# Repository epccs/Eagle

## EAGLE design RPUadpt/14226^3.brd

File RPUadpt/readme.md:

[RPUadpt]

Shield to interface microcontrollers to a managed multidrop serial.

[RPUadpt]: https://github.com/epccs/RPUadpt/

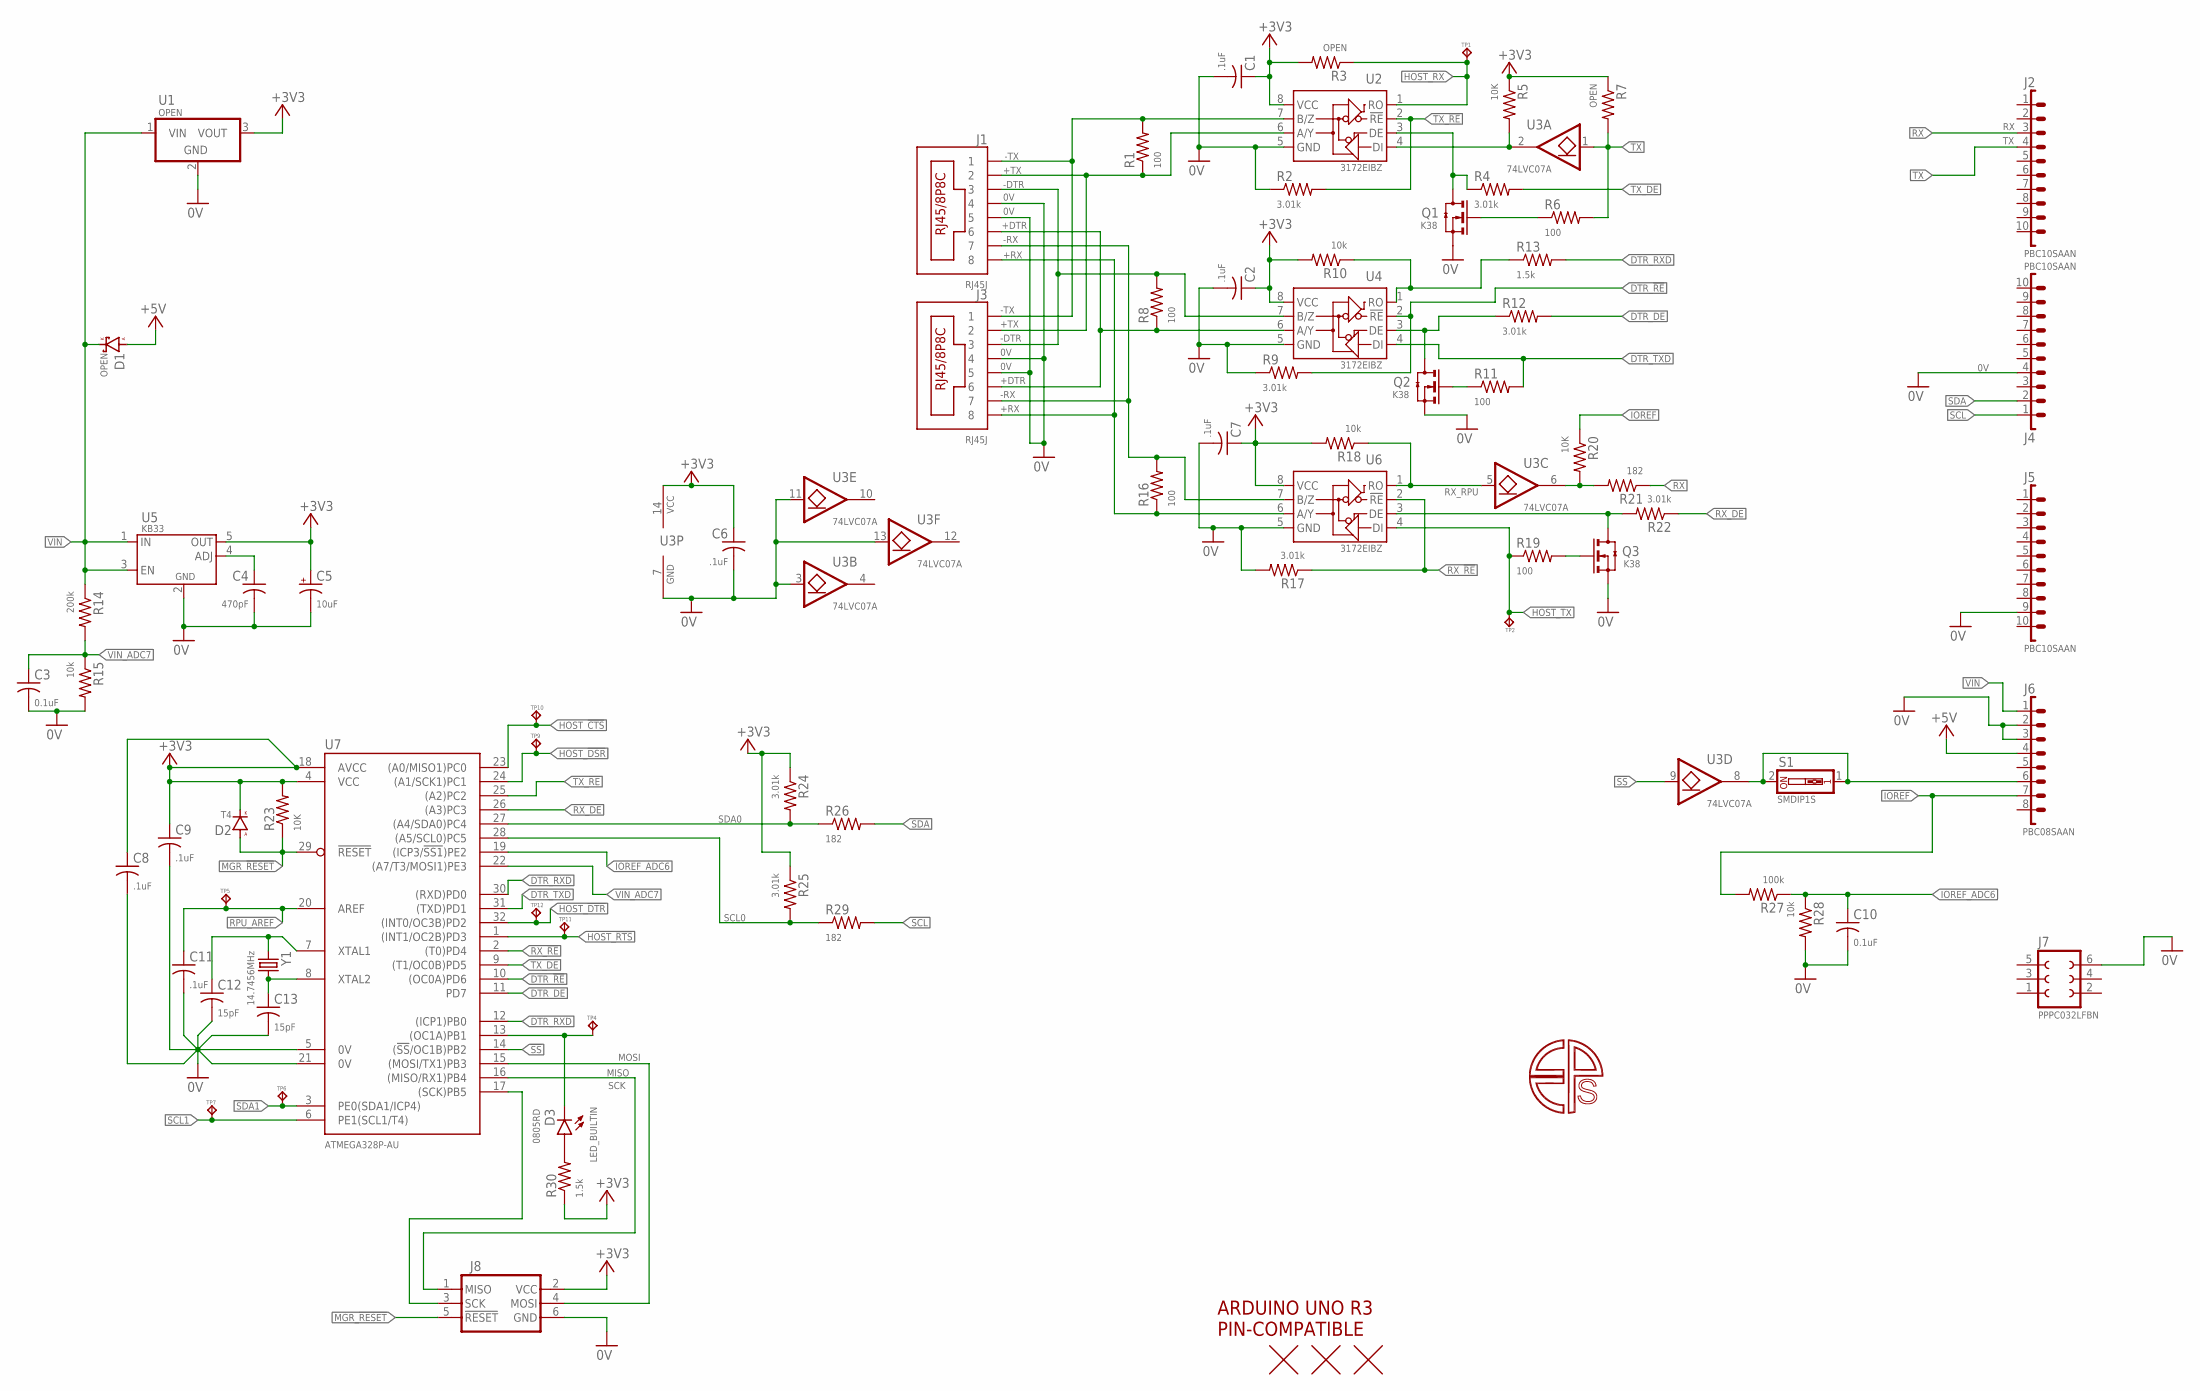
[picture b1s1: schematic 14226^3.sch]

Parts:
C1, C2, C6, C7, C8, C9, C11: .1uF; C0603(1608)
C3, C10: 0.1uF; C0603(1608)
C4: 470pF; C0603(1608)
C5: 10uF; 3216
C12, C13: 15pF; C0603(1608)
D1: OPEN; SMA
D2: T4; SOD123
D3: 0805RD; C0805(2012)
J1, J3: RJ45J; RJ45-8HZT
J2, J4, J5: PBC10SAAN; 1X10
J6: PBC08SAAN; 1X8
J7: PPPC032LFBN; F2X3
J8: ISP-SPIPTH; ISP
Q1, Q2, Q3: K38; SOT23
R1, R6, R8, R11, R16, R19: 100; C0805(2012)
R2, R4, R9, R12, R17, R22, R24, R25: 3.01k; C0805(2012)
R3, R7: OPEN; C0805(2012)
R5, R20, R23: 10K; C0805(2012)
R10, R15, R18, R28: 10k; C0805(2012)
R13, R30: 1.5k; C0805(2012)
R14: 200k; C0805(2012)
R21, R26, R29: 182; C0805(2012)
R27: 100k; C0805(2012)
S1: SMDIP1S; SMD-DIPSWITCH-1
TP1, TP2, TP4, TP5, TP6, TP7, TP9, TP10, TP11, TP12: TPPAD1-08; P1-08
U1: OPEN; OKI-78SR-H
U2, U4, U6: 3172EIBZ; SOIC8
U3: 74LVC07A; 14SOIC
U5: KB33; SOT23-5,SOT25
U7: ATMEGA328P-AU; TQFP32-08
U$1: ARDUINO-UNO; ARDUINO_UNO
U$2, U$3, U$4: FIDUCIAL1.27; FIDUCIAL-1.27
Y1: 14.7456MHz; CSM-3X

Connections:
0V: C1.2, C2.2, C3.2, C4.2, C5.-, C6.2, C7.2, C8.2, C9.2, C10.2, C11.2, C12.2, C13.2, J1.4, J1.5, J3.4, J3.5, J4.4, J5.9, J6.2, J6.3, J7.6, J8.6 (GND), Q1.2(S) (S), Q2.2(S) (S), Q3.2(S) (S), R2.1, R9.1, R15.2, R17.2, R28.2, U1.2 (GND), U2.5 (GND), U3.3 (I), U3.7 (GND), U3.11 (I), U3.13 (I), U4.5 (GND), U5.2 (GND), U6.5 (GND), U7.5 (0V), U7.21 (0V)
!SS!: U3.9 (I), U7.14 ((!SS!/OC1B)PB2)
+3V3: C1.1, C2.1, C5.+, C6.1, C7.1, C8.1, C9.1, D2.C (K), J8.2 (VCC), R3.2, R5.1, R7.1, R10.2, R18.2, R23.2, R24.1, R25.1, R30.1, U1.3 (VOUT), U2.8 (VCC), U3.14 (VCC), U4.8 (VCC), U5.5 (OUT), U6.8 (VCC), U7.4 (VCC), U7.18 (AVCC)
+5V: D1.A, J6.4
+DTR: J1.6, J3.6, R8.1, U4.6 (A/Y)
+RX: J1.8, J3.8, R16.1, U6.6 (A/Y)
+TX: J1.2, J3.2, R1.1, U2.6 (A/Y)
-DTR: J1.3, J3.3, R8.2, U4.7 (B/Z)
-RX: J1.7, J3.7, R16.2, U6.7 (B/Z)
-TX: J1.1, J3.1, R1.2, U2.7 (B/Z)
DTR_!RE: R9.2, U4.2 (!RE), U7.10 ((OC0A)PD6)
DTR_DE: R12.2, U7.11 (PD7)
DTR_RXD: R13.2, U7.12 ((ICP1)PB0), U7.30 ((RXD)PD0)
DTR_TXD: R11.2, U4.4 (DI), U7.31 ((TXD)PD1)
HOST_!CTS: TP10.TP, U7.23 ((A0/MISO1)PC0)
HOST_!DSR: TP9.TP, U7.24 ((A1/SCK1)PC1)
HOST_!DTR: TP12.TP, U7.32 ((INT0/OC3B)PD2)
HOST_!RTS: TP11.TP, U7.1 ((INT1/OC2B)PD3)
HOST_RX: R3.1, TP1.TP, U2.1 (RO)
HOST_TX: R19.1, TP2.TP, U6.4 (DI)
IOREF: J6.7, R20.1, R27.2
IOREF_ADC6: C10.1, R27.1, R28.1, U7.19 ((ICP3/!SS1!)PE2)
LED_BUILTIN: D3.K, TP4.TP, U7.13 ((OC1A)PB1)
MGR_!RESET: D2.A, J8.5 (!RESET), R23.1, U7.29 (!RESET)
MISO: J8.1 (MISO), U7.16 ((MISO/RX1)PB4)
MOSI: J8.4 (MOSI), U7.15 ((MOSI/TX1)PB3)
unnamed: J6.6, S1.1, S1.2, U3.8 (O)
unnamed: R20.2, R21.2, U3.6 (O)
unnamed: Q3.3(D) (D), R22.2, U6.3 (DE)
unnamed: Q1.1(G) (G), R6.1
unnamed: Q1.3(D) (D), R4.1, U2.3 (DE)
unnamed: R10.1, R13.1, U4.1 (RO)
unnamed: Q2.3(D) (D), R12.1, U4.3 (DE)
unnamed: Q2.1(G) (G), R11.1
unnamed: C4.1, U5.4 (ADJ)
unnamed: Q3.1(G) (G), R19.2
unnamed: D3.A, R30.2
RPU_AREF: C11.1, TP5.TP, U7.20 (AREF)
RX: J2.3, R21.1
RX_!RE: R17.1, U6.2 (!RE), U7.2 ((T0)PD4)
RX_DE: R22.1, U7.26 ((A3)PC3)
RX_RPU: R18.1, U3.5 (I), U6.1 (RO)
SCK: J8.3 (SCK), U7.17 ((SCK)PB5)
SCL: J4.1, R29.2
SCL0: R25.2, R29.1, U7.28 ((A5/SCL0)PC5)
SCL1: TP7.TP, U7.6 (PE1(SCL1/T4))
SDA: J4.2, R26.2
SDA0: R24.2, R26.1, U7.27 ((A4/SDA0)PC4)
SDA1: TP6.TP, U7.3 (PE0(SDA1/ICP4))
TX: J2.4, R6.2, R7.2, U3.1 (I)
TX_!RE: R2.2, U2.2 (!RE), U7.25 ((A2)PC2)
TX_DE: R4.2, U7.9 ((T1/OC0B)PD5)
TX_RPU: R5.2, U2.4 (DI), U3.2 (O)
VIN: D1.K, J6.1, R14.1, U1.1 (VIN), U5.1 (IN), U5.3 (EN)
VIN_ADC7: C3.1, R14.2, R15.1, U7.22 ((A7/T3/MOSI1)PE3)
XTAL1: C12.1, U7.7 (XTAL1), Y1.1
XTAL2: C13.1, U7.8 (XTAL2), Y1.2

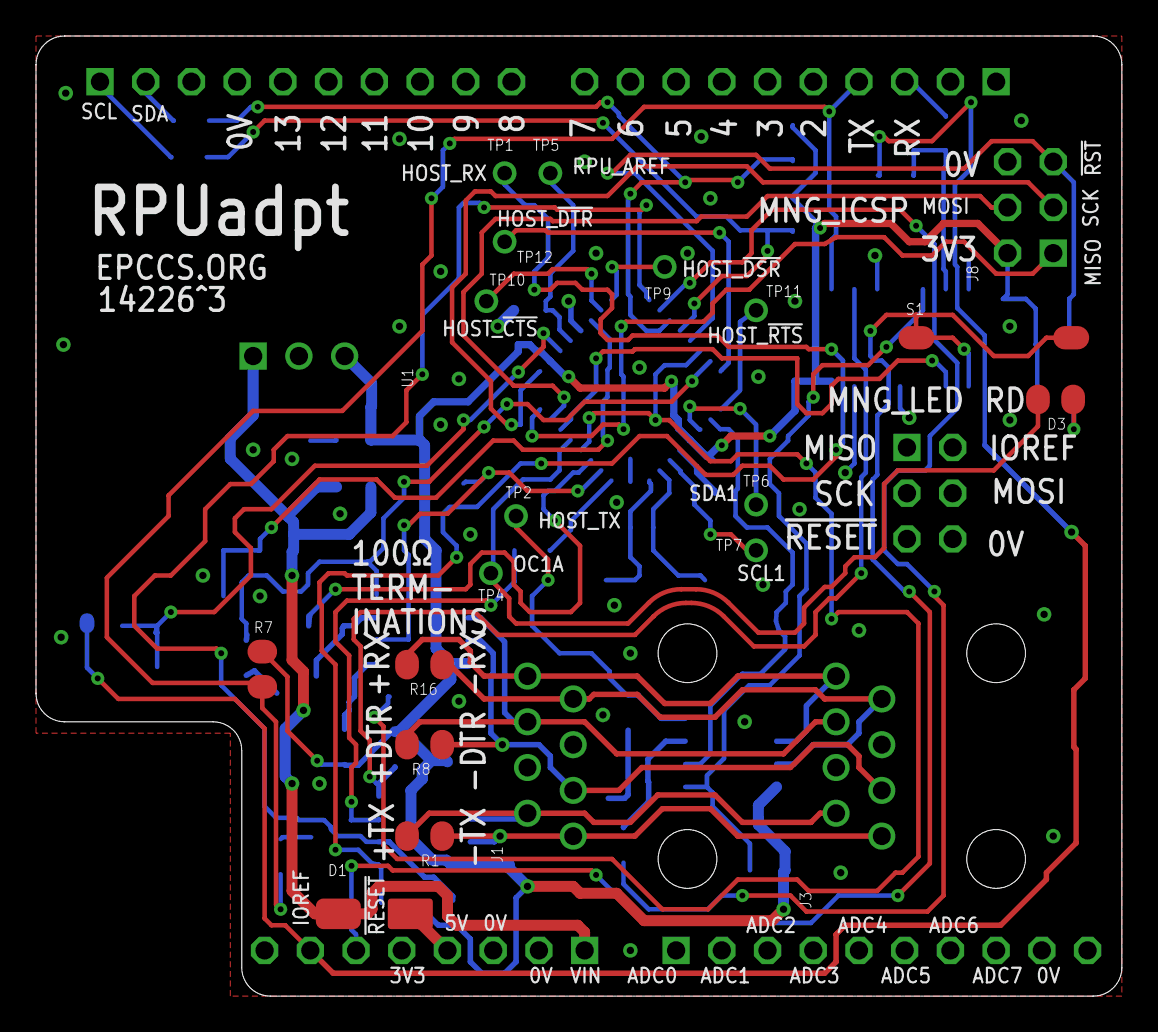
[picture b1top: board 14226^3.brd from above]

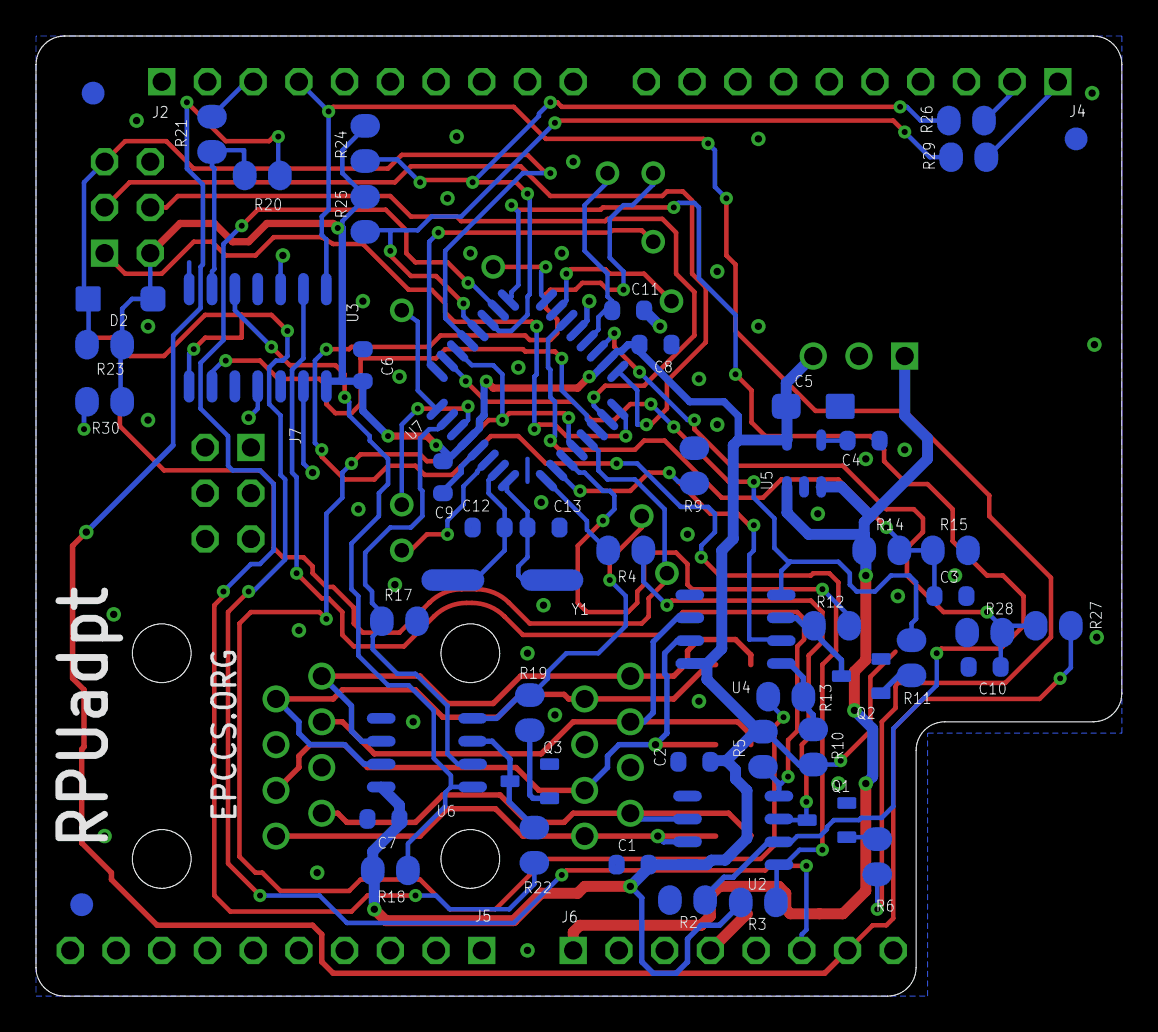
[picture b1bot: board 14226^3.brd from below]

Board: 2 copper layers, 60.3 x 53.3 mm, 80 parts (58 on the bottom side), 57 nets.

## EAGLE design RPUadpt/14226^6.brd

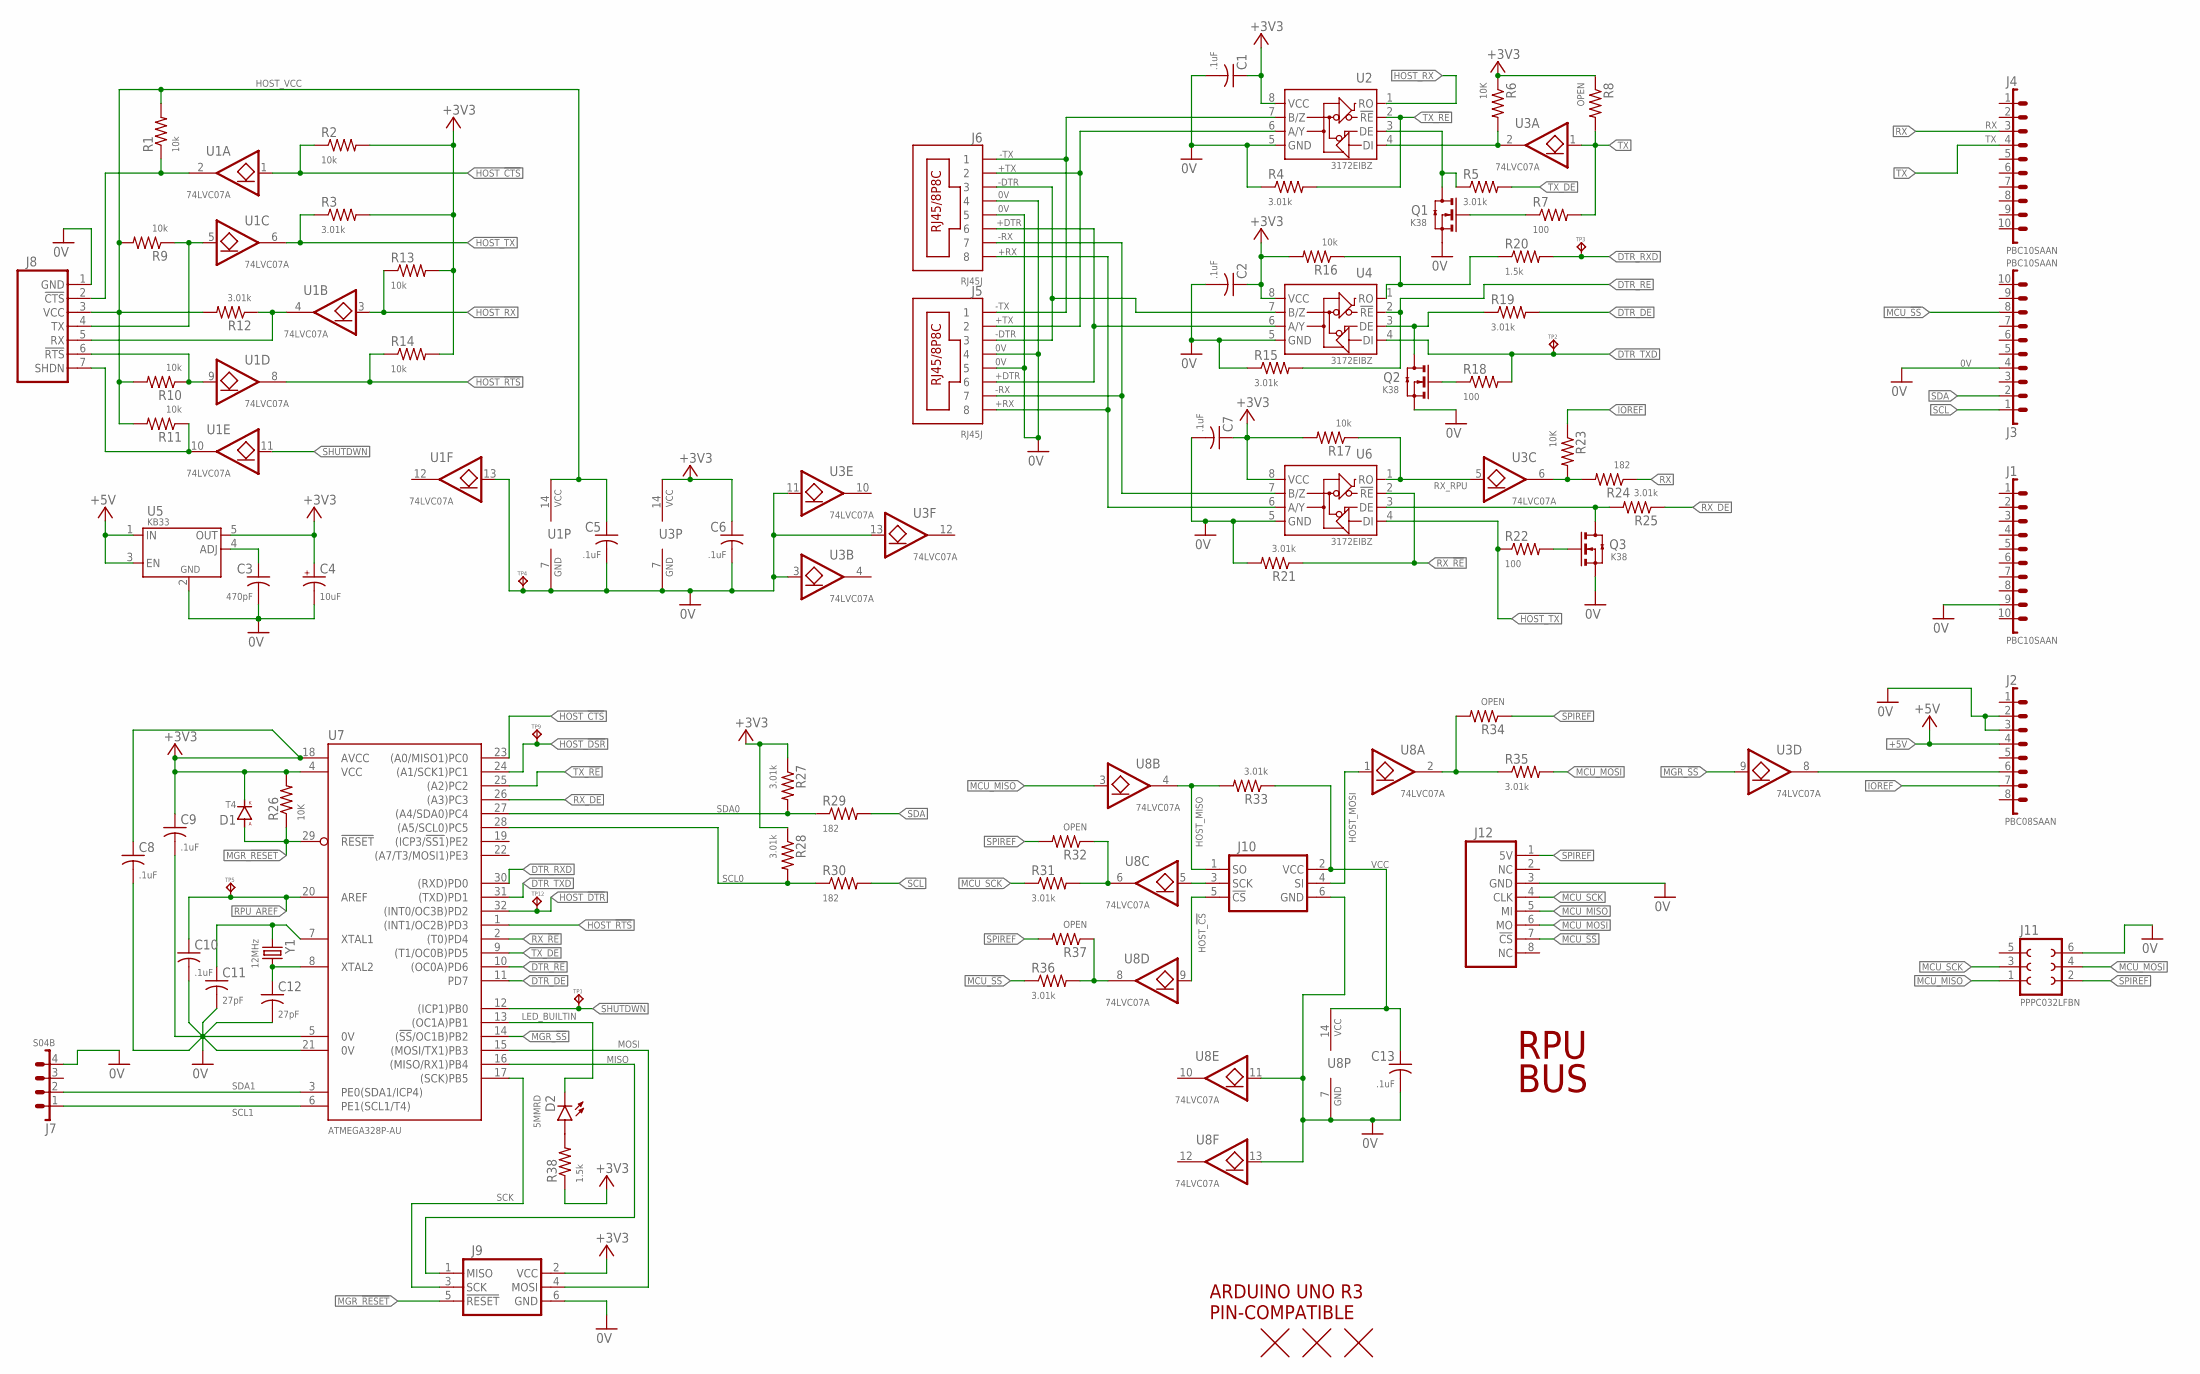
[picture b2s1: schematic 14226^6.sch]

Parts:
C1, C2, C5, C6, C7, C8, C9, C10, C13: .1uF; C0603(1608)
C3: 470pF; C0603(1608)
C4: 10uF; 3216
C11, C12: 27pF; C0603(1608)
D1: T4; SOD123
D2: 5MMRD; LED5MM
J1, J3, J4: PBC10SAAN; 1X10
J2: PBC08SAAN; 1X8
J5, J6: RJ45J; RJ45-8HZT
J7: S04B; B04B
J8: FTDI-FRIEND
J9: ISP-SPIPTH; ISP
J10: SPI; ISP
J11: PPPC032LFBN; F2X3
J12: MICRO-SD
Q1, Q2, Q3: K38; SOT23
R1, R2, R9, R10, R11, R13, R14, R16, R17: 10k; C0805(2012)
R3, R4, R5, R12, R15, R19, R21, R25, R27, R28, R31, R33, R35, R36: 3.01k; C0805(2012)
R6, R23, R26: 10K; C0805(2012)
R7, R18, R22: 100; C0805(2012)
R8, R32, R34, R37: OPEN; C0805(2012)
R20, R38: 1.5k; C0805(2012)
R24, R29, R30: 182; C0805(2012)
TP1, TP2, TP3, TP4, TP5, TP9, TP12: TPPAD1-08; P1-08
U1, U3, U8: 74LVC07A; 14SOIC
U2, U4, U6: 3172EIBZ; SOIC8
U5: KB33; SOT23-5,SOT25
U7: ATMEGA328P-AU; TQFP32-08
U$1: ARDUINO-UNO; ARDUINO_UNO
U$2, U$3, U$4: FIDUCIAL1.27; FIDUCIAL-1.27
Y1: 12MHz; CSM-3X

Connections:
0V: C1.2, C2.2, C3.2, C4.-, C5.2, C6.2, C7.2, C8.2, C9.2, C10.2, C11.2, C12.2, C13.2, J1.9, J2.2, J2.3, J3.4, J5.4, J5.5, J6.4, J6.5, J7.4, J8.1 (GND), J9.6 (GND), J10.6 (GND), J11.6, J12.3 (GND), Q1.2(S) (S), Q2.2(S) (S), Q3.2(S) (S), R4.1, R15.1, R21.2, TP4.TP, U1.7 (GND), U1.13 (I), U2.5 (GND), U3.3 (I), U3.7 (GND), U3.11 (I), U3.13 (I), U4.5 (GND), U5.2 (GND), U6.5 (GND), U7.5 (0V), U7.21 (0V), U8.7 (GND), U8.11 (I), U8.13 (I)
+3V3: C1.1, C2.1, C4.+, C6.1, C7.1, C8.1, C9.1, D1.C (K), J9.2 (VCC), R2.2, R3.2, R6.1, R8.1, R13.2, R14.2, R16.2, R17.2, R26.2, R27.1, R28.1, R38.1, U2.8 (VCC), U3.14 (VCC), U4.8 (VCC), U5.5 (OUT), U6.8 (VCC), U7.4 (VCC), U7.18 (AVCC)
+5V: J2.4, U5.1 (IN), U5.3 (EN)
+DTR: J5.6, J6.6, U4.6 (A/Y)
+RX: J5.8, J6.8, U6.6 (A/Y)
+TX: J5.2, J6.2, U2.6 (A/Y)
-DTR: J5.3, J6.3, U4.7 (B/Z)
-RX: J5.7, J6.7, U6.7 (B/Z)
-TX: J5.1, J6.1, U2.7 (B/Z)
DTR_!RE: R15.2, U4.2 (!RE), U7.10 ((OC0A)PD6)
DTR_DE: R19.2, U7.11 (PD7)
DTR_RXD: R20.2, TP3.TP, U7.30 ((RXD)PD0)
DTR_TXD: R18.2, TP2.TP, U4.4 (DI), U7.31 ((TXD)PD1)
HOST_!CS: J10.5 (!CS), U8.9 (I)
HOST_!CTS: R2.1, U1.1 (I), U7.23 ((A0/MISO1)PC0)
HOST_!DSR: TP9.TP, U7.24 ((A1/SCK1)PC1)
HOST_!DTR: TP12.TP, U7.32 ((INT0/OC3B)PD2)
HOST_!RTS: R14.1, U1.8 (O), U7.1 ((INT1/OC2B)PD3)
HOST_MISO: J10.1 (SO), R33.2, U8.4 (O)
HOST_MOSI: J10.4 (SI), U8.1 (I)
HOST_RX: R13.1, U1.3 (I), U2.1 (RO)
HOST_SCK: J10.3 (SCK), U8.5 (I)
HOST_TX: R3.1, R22.1, U1.6 (O), U6.4 (DI)
HOST_VCC: C5.1, J8.3 (VCC), R1.2, R9.2, R10.2, R11.2, R12.2, U1.14 (VCC)
IOREF: J2.7, R23.1
LED_BUILTIN: D2.K, U7.13 ((OC1A)PB1)
MCU_!SS!: J3.8, J12.7 (!CS), R36.1
MCU_MISO: J11.1, J12.5 (MI), U8.3 (I)
MCU_MOSI: J11.4, J12.6 (MO), R35.2
MCU_SCK: J11.3, J12.4 (CLK), R31.1
MGR_!RESET: D1.A, J9.5 (!RESET), R26.1, U7.29 (!RESET)
MGR_!SS!: U3.9 (I), U7.14 ((!SS!/OC1B)PB2)
MISO: J9.1 (MISO), U7.16 ((MISO/RX1)PB4)
MOSI: J9.4 (MOSI), U7.15 ((MOSI/TX1)PB3)
unnamed: J2.6, U3.8 (O)
unnamed: R34.2, R35.1, U8.2 (O)
unnamed: D2.A, R38.2
unnamed: R31.2, R32.1, U8.6 (O)
unnamed: R23.2, R24.2, U3.6 (O)
unnamed: Q3.3(D) (D), R25.2, U6.3 (DE)
unnamed: R36.2, R37.1, U8.8 (O)
unnamed: Q1.1(G) (G), R7.1
unnamed: Q1.3(D) (D), R5.1, U2.3 (DE)
unnamed: R16.1, R20.1, U4.1 (RO)
unnamed: Q2.3(D) (D), R19.1, U4.3 (DE)
unnamed: Q2.1(G) (G), R18.1
unnamed: C3.1, U5.4 (ADJ)
unnamed: Q3.1(G) (G), R22.2
RPU_AREF: C10.1, TP5.TP, U7.20 (AREF)
RX: J4.3, R24.1
RX_!RE: R21.1, U6.2 (!RE), U7.2 ((T0)PD4)
RX_DE: R25.1, U7.26 ((A3)PC3)
RX_RPU: R17.1, U3.5 (I), U6.1 (RO)
SCK: J9.3 (SCK), U7.17 ((SCK)PB5)
SCL: J3.1, R30.2
SCL0: R28.2, R30.1, U7.28 ((A5/SCL0)PC5)
SCL1: J7.1, U7.6 (PE1(SCL1/T4))
SDA: J3.2, R29.2
SDA0: R27.2, R29.1, U7.27 ((A4/SDA0)PC4)
SDA1: J7.2, U7.3 (PE0(SDA1/ICP4))
SHUTDWN: TP1.TP, U1.11 (I), U7.12 ((ICP1)PB0)
SPIREF: J11.2, J12.1 (5V), R32.2, R34.1, R37.2
TX: J4.4, R7.2, R8.2, U3.1 (I)
TX_!RE: R4.2, U2.2 (!RE), U7.25 ((A2)PC2)
TX_DE: R5.2, U7.9 ((T1/OC0B)PD5)
TX_RPU: R6.2, U2.4 (DI), U3.2 (O)
VCC: C13.1, J10.2 (VCC), R33.1, U8.14 (VCC)
XTAL1: C11.1, U7.7 (XTAL1), Y1.1
XTAL2: C12.1, U7.8 (XTAL2), Y1.2
_HOST_!CTS: J8.2 (!CTS), R1.1, U1.2 (O)
_HOST_!RTS: J8.6 (!RTS), R10.1, U1.9 (I)
_HOST_RX: J8.5 (RX), R12.1, U1.4 (O)
_HOST_SHDN: J8.7 (SHDN), R11.1, U1.10 (O)
_HOST_TX: J8.4 (TX), R9.1, U1.5 (I)

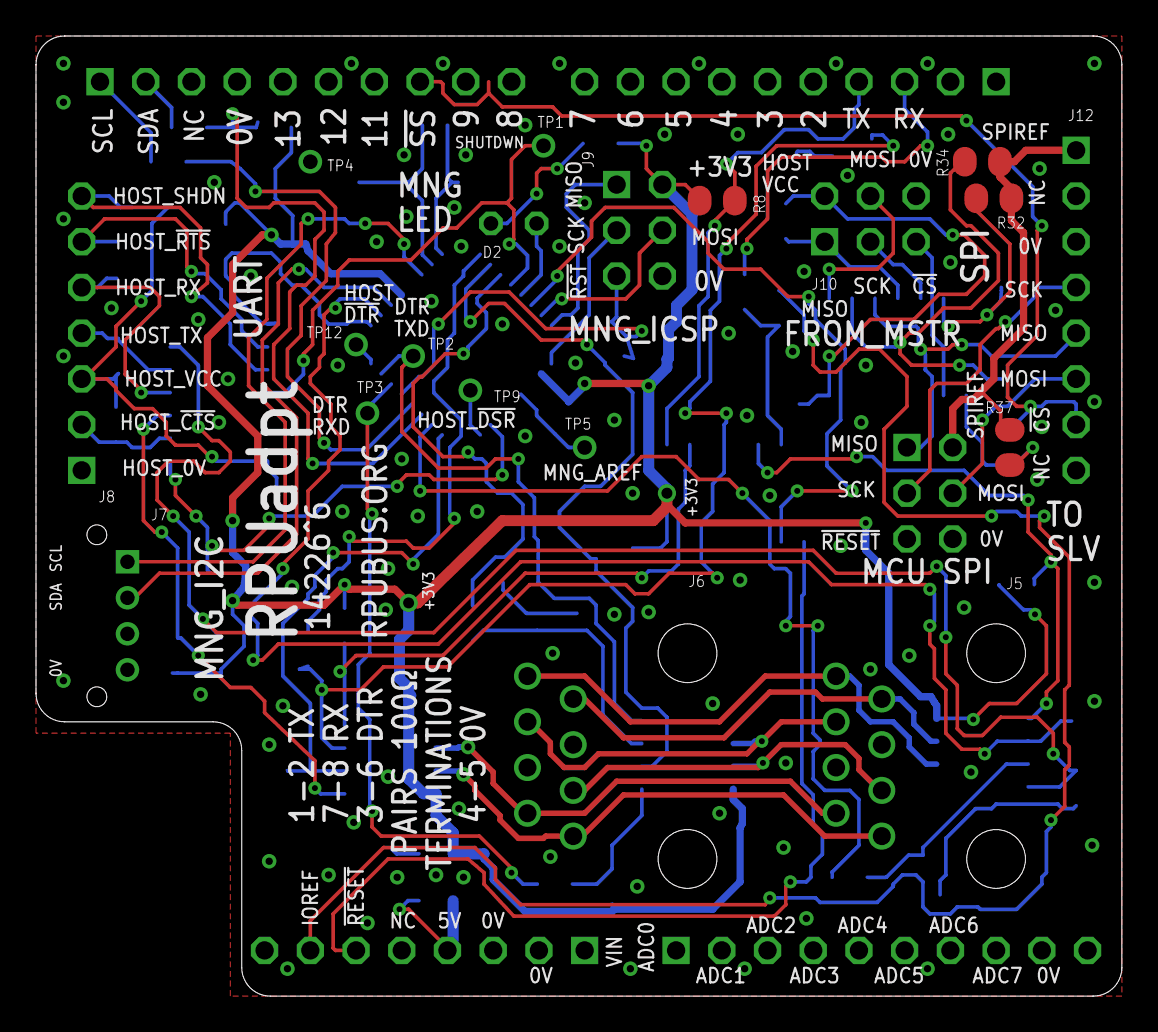
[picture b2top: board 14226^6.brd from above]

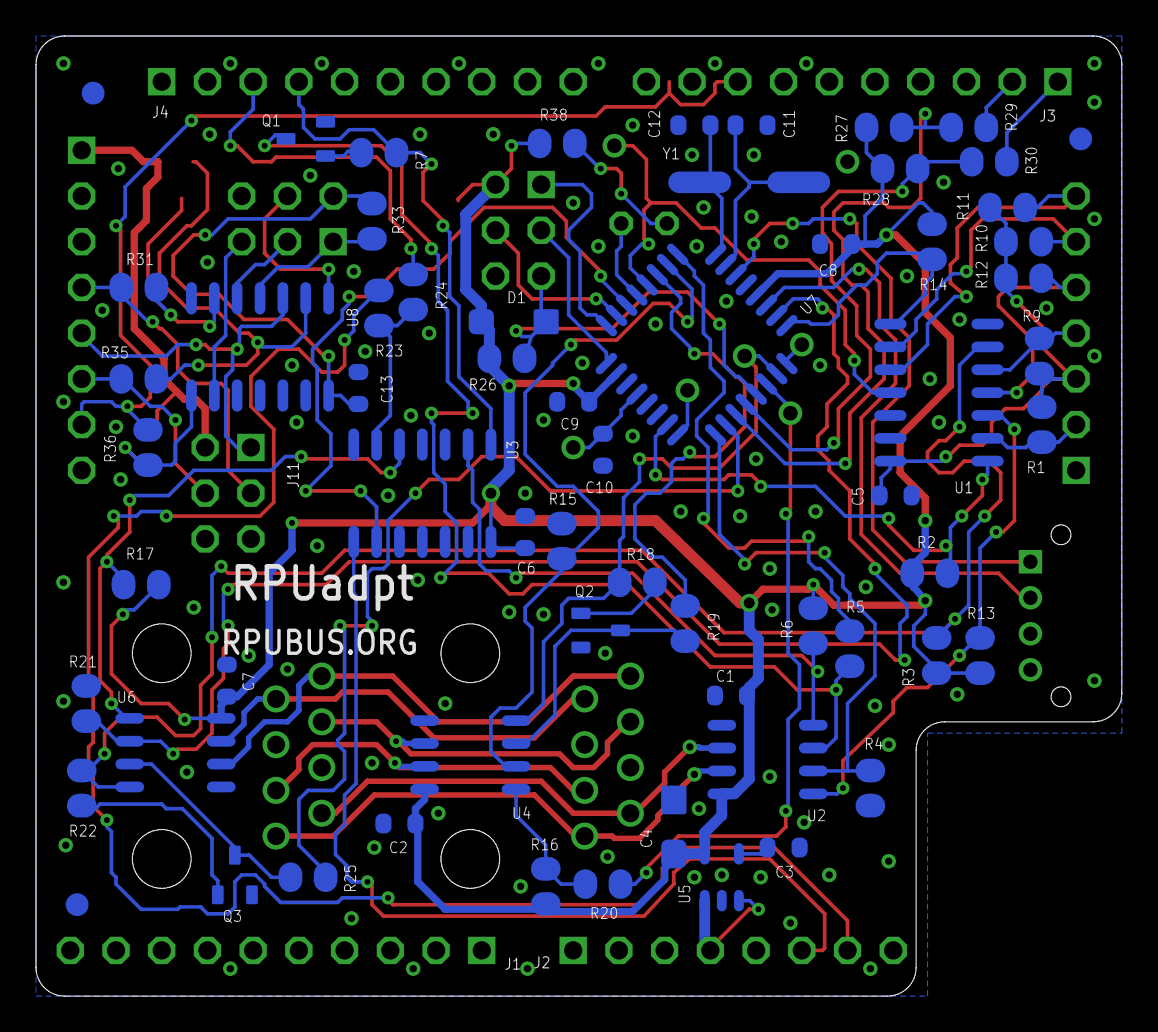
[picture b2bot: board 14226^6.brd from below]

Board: 2 copper layers, 60.3 x 53.3 mm, 88 parts (68 on the bottom side), 74 nets.

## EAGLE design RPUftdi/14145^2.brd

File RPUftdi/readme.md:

[RPUftdi]

Shield to interface a host USB to a managed multidrop serial.

[RPUftdi]: https://github.com/epccs/RPUftdi/

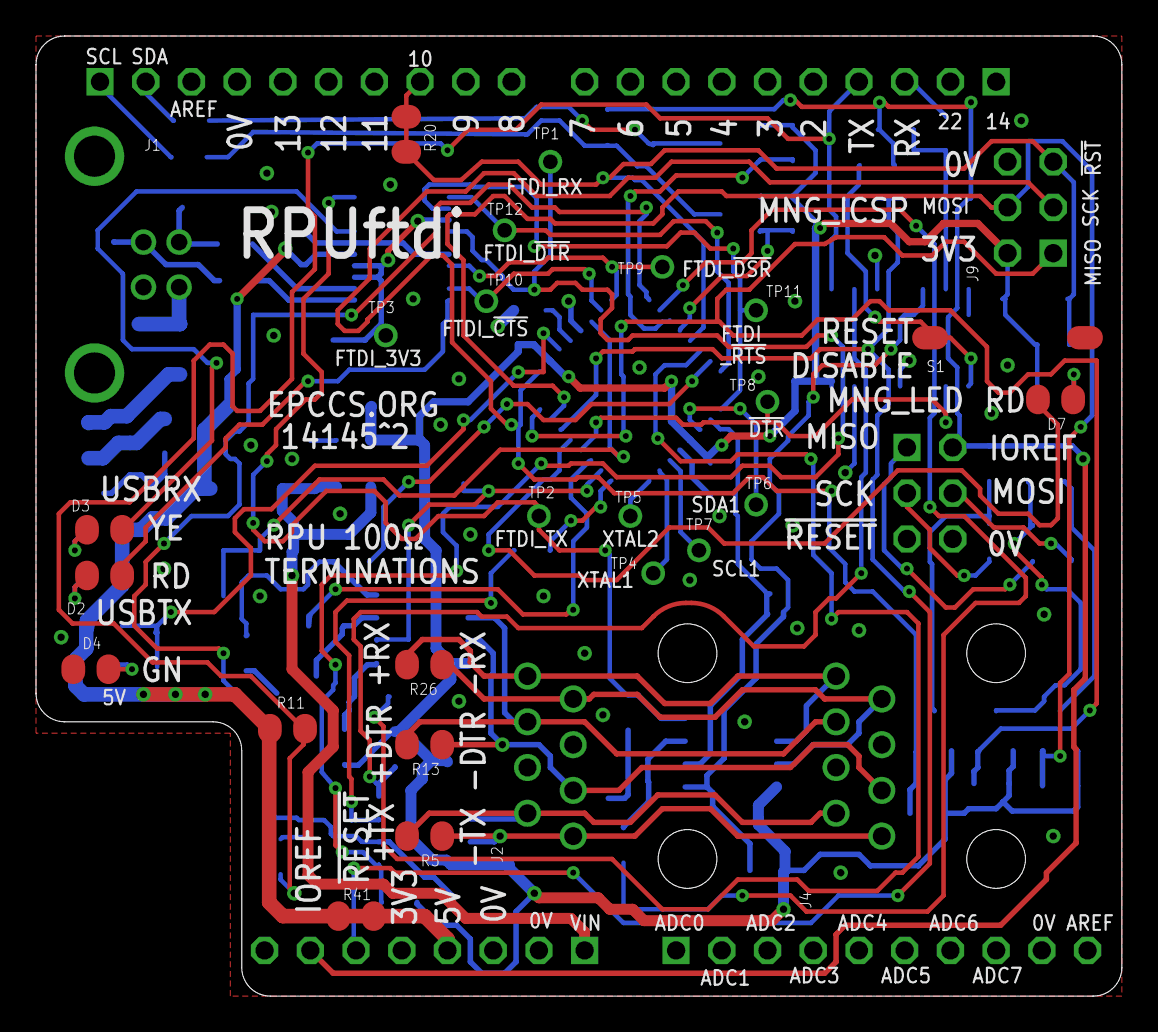
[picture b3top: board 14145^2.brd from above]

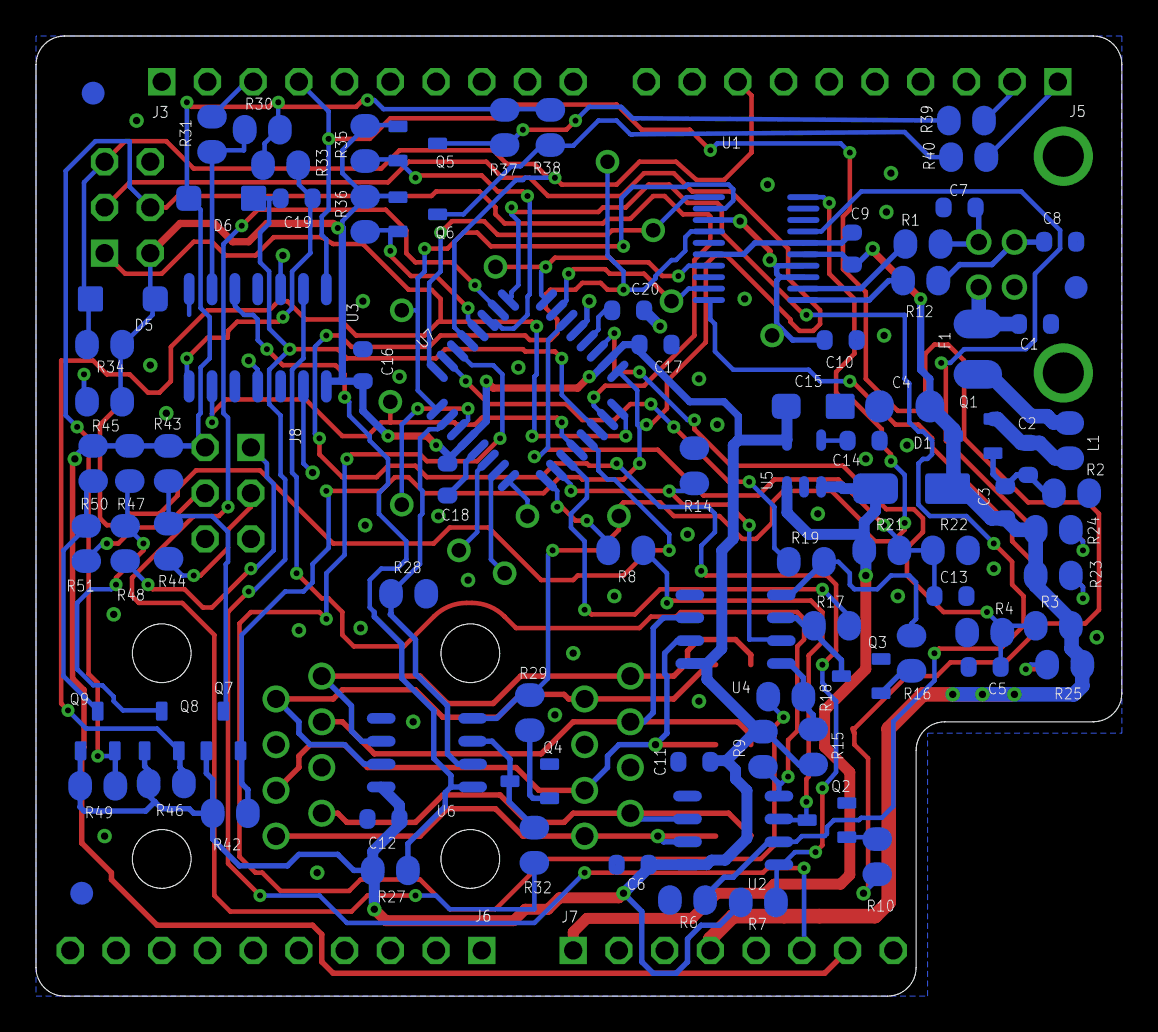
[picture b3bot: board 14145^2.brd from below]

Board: 2 copper layers, 60.3 x 53.3 mm, 122 parts (94 on the bottom side), 81 nets.

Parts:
C1, C2, C5, C9, C10, C13: 0.1uF; C0603(1608)
C3: 0.022uF; C0603(1608)
C4: 4.7uF; C1206(3216)
C6, C11, C12, C16, C17, C18, C19, C20: .1uF; C0603(1608)
C7, C8: 47pF; C0603(1608)
C14: 470pF; C0603(1608)
C15: 10uF; 3216
D1: SQ4; SMA
D2, D7: 0805RD; C0805(2012)
D3: 0805YE; C0805(2012)
D4: 0805GN; C0805(2012)
D5, D6: T4; SOD123
F1: M; C1210(3225)
J1: B; USB-B-PTH
J2, J4: RJ45J; RJ45-8HZT
J3, J5, J6: PBC10SAAN; 1X10
J7: PBC08SAAN; 1X8
J8: PPPC032LFBN; F2X3
J9: ISP
L1: MH2029-300Y; C0805(2012)
Q1: DMB; SOT23
Q2, Q3, Q4, Q5, Q6, Q7, Q8, Q9: K38; SOT23
R1, R12: 27; C0805(2012)
R2: 5.62k; C0805(2012)
R3, R33: 100k; C0805(2012)
R4, R7, R15, R22, R27, R35, R36, R37, R38, R42, R43, R46, R47, R49, R50: 10k; C0805(2012)
R5, R10, R13, R16, R26, R29: 100; C0805(2012)
R6, R8, R14, R17, R28, R32: 3.01k; C0805(2012)
R9, R30, R34: 10K; C0805(2012)
R11: OPEN; C0805(2012)
R18, R19, R23, R24, R25, R45: 1.5k; C0805(2012)
R20, R41: JMP; C0805(2012)
R21: 200k; C0805(2012)
R31, R39, R40, R44, R48, R51: 180; C0805(2012)
S1: SMDIP1S; SMD-DIPSWITCH-1
TP1, TP2, TP3, TP4, TP5, TP6, TP7, TP8, TP9, TP10, TP11, TP12: TPPAD1-08; P1-08
U1: FT231X; 20SSOP
U2, U4, U6: 3172EIBZ; SOIC8
U3: 74LVC07A; 14SOIC
U5: KB33; SOT23-5,SOT25
U7: ATMEGA328P-AU; TQFP32-08
U$1: ARDUINO-UNO; ARDUINO_UNO
U$2, U$3, U$4: FIDUCIAL1.27; FIDUCIAL-1.27

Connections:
0V: C1.2, C4.2, C5.2, C6.2, C7.2, C8.2, C9.2, C10.2, C11.2, C12.2, C13.2, C14.2, C15.-, C16.2, C17.2, C18.2, C20.2, D4.K, J1.4, J1.S1, J1.S2, J2.4, J2.5, J4.4, J4.5, J5.4, J6.9, J7.2, J7.3, J8.6, J9.6, Q2.2(S), Q3.2(S), Q4.2(S), R2.2, R4.2, R6.1, R14.1, R22.2, R28.2, S1.1, U1.6, U1.16, U2.5, U3.3, U3.7, U3.11, U3.13, U4.5, U5.2, U6.5, U7.5, U7.21
!DTR!: TP8.TP, U3.9, U7.12
+3V3: C6.1, C11.1, C12.1, C15.+, C16.1, C17.1, C18.1, D5.C, J9.2, Q5.1(G), Q6.1(G), Q7.1(G), Q8.1(G), Q9.1(G), R7.2, R9.1, R15.2, R27.2, R34.2, R35.1, R36.1, R42.1, R45.1, R46.1, R49.1, U2.8, U3.14, U4.8, U5.5, U6.8, U7.4, U7.18
+5V: C3.1, C4.1, C9.1, D1.A, J7.4, Q1.3(D), R3.2, R11.1, R23.2, R24.2, R25.2, R41.1, R41.2, U1.15
+DTR: J2.6, J4.6, R13.1, U4.6
+RX: J2.8, J4.8, R26.1, U6.6
+TX: J2.2, J4.2, R5.1, U2.6
-DTR: J2.3, J4.3, R13.2, U4.7
-RX: J2.7, J4.7, R26.2, U6.7
-TX: J2.1, J4.1, R5.2, U2.7
BRD_MISO: J8.1, R48.2
BRD_MOSI: J8.4, R51.2
BRD_SCK: J8.3, R44.2
CCRST: C19.1, R33.1, S1.2, U3.8
D+: C8.1, J1.3, R12.1
D-: C7.1, J1.2, R1.1
DTR_!RE: R14.2, U4.2, U7.10
DTR_DE: R17.2, U7.11
DTR_RXD: R18.2, U7.30
DTR_TXD: R19.2, U7.31
FT3V3: C10.1, TP3.TP, U1.3, U1.13, U1.14
FTDI_!CTS: TP10.TP, U1.9, U7.23
FTDI_!DSR: TP9.TP, U1.7, U7.24
FTDI_!DTR: TP12.TP, U1.1, U7.32
FTDI_!RTS: TP11.TP, U1.2, U7.1
FTDI_RX: R7.1, TP1.TP, U1.4, U2.1
FTDI_TX: R29.1, TP2.TP, U1.20, U6.4
IOREF: D6.C, J7.7, J8.2, R30.1, R33.2, R37.1, R38.1, R43.1, R47.1, R50.1
LED_BUILTIN: D7.K, U7.13
MGR_!RESET: D5.A, J5.8, J9.5, R20.1, R20.2, R34.1, U7.29
MISO: J9.1, Q8.2(S), R46.2, U7.16
MOSI: J9.4, Q9.2(S), R49.2, U7.15
unnamed: Q6.3(D), R38.2, R40.1
unnamed: Q5.3(D), R37.2, R39.1
unnamed: TP4.TP, U7.7
unnamed: C1.1, F1.1, J1.1
unnamed: F1.2, L1.1
unnamed: D3.A, R24.1
unnamed: D2.K, U1.10
unnamed: D3.K, U1.17
unnamed: TP5.TP, U7.8
unnamed: R30.2, R31.2, U3.6
unnamed: Q4.3(D), R32.2, U6.3
unnamed: R1.2, U1.12
unnamed: R12.2, U1.11
unnamed: D4.A, R25.1
unnamed: Q2.1(G), R10.1
unnamed: D2.A, R23.1
unnamed: Q2.3(D), R8.1, U2.3
unnamed: R15.1, R18.1, U4.1
unnamed: Q3.3(D), R17.1, U4.3
unnamed: R16.2, R19.1, U4.4
unnamed: Q3.1(G), R16.1
unnamed: Q7.3(D), R43.2, R44.1
unnamed: C14.1, U5.4
unnamed: Q4.1(G), R29.2
unnamed: C2.1, L1.2, Q1.2(S)
unnamed: C2.2, C3.2, Q1.1(G), R2.1
unnamed: D7.A, R45.2
unnamed: Q9.3(D), R50.2, R51.1
unnamed: Q8.3(D), R47.2, R48.1
RPU_AREF: C20.1, U7.20
RX: J3.3, R31.1
RX_!RE: R28.1, U6.2, U7.2
RX_DE: R32.1, U7.26
RX_RPU: R27.1, U3.5, U6.1
SCK: J9.3, Q7.2(S), R42.2, U7.17
SCL: J5.1, R40.2
SCL0: Q6.2(S), R36.2, U7.28
SCL1: TP7.TP, U7.6
SDA: J5.2, R39.2
SDA0: Q5.2(S), R35.2, U7.27
SDA1: TP6.TP, U7.3
SS: C19.2, D6.A, J7.6, U7.14
TX: J3.4, R10.2, R11.2, U3.1
TX_!RE: R6.2, U2.2, U7.25
TX_DE: R8.2, U7.9
TX_RPU: R9.2, U2.4, U3.2
USB5V_ADC6: C5.1, R3.1, R4.1, U7.19
VIN: D1.K, J7.1, R21.1, U5.1, U5.3
VIN_ADC7: C13.1, R21.2, R22.1, U7.22

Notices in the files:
parts and their libraries:
P-DCDC: Copyright (C) 2013 Ronald Steven Sutherland
under the terms of the GNU Free Documentation License, Version 1.2 or
any later version published by the Free Software Foundation; with no
C-C: Released under the Creative Commons
Attribution Share-Alike 3.0 License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
